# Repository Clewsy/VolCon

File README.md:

# volcon

A USB volume controller that uses a VCR head drum for the knob.

More photos and information can be found [here][link_clews_volcon].

Proudly mentioned at [hackaday.com][link_web_hackaday_volcon], and also on [episode 106][link_web_hackaday_podcast_106] of the [hackaday podcast][link_web_hackaday_podcast].

## Revision 1

This project began as an experiment when I wanted to learn how an optical [quadrature encoder][link_web_quadrature_encoder] worked (FYI, 2-bit [Gray code][link_web_gray_code]).

It transformed into a learning experience around USB - specifically the [HID protocol][link_web_hid].  Ultimately I ended up with a simple gadget that now sits on my desk and allows me to control the PC volume.

A salvaged optical encoder was used to detect rotation along with a reclaimed [head drum][link_web_head_drum] from a [VCR][link_web_vcr] which was repurposed as a control knob. I very much like the smooth bearings combined with the heavy mass that let the drum spin forever.

Key concepts for the project were:

* The optical encoder parts (sensors and disk) were salvaged from an old track-ball.
* The "knob" was made from the head drum of a VHS VCR (remember those?). This is the part that spins and is used to adjust volume on my PC.
* This assembly is mounted to a custom PCB with some nylon stand-offs. The PCB became the base of the whole unit.
* The optical disk was fixed to the shaft and optical sensors mounted to one of the nylon standoffs.
* I cut some wooden rings to enclose the electronics and the base of the VCR drum.
* The original custom PCB was designed in eagle and etched at home from some single-sided copper-clad board. The circuit was designed around an AVR AT90usb162.
* The code is written in C and implements the LUFA library developed by Dean Camera.
* The whole unit plugs into a PC via USB and is automatically identified as a HID - no drivers required (tested in Debian, Ubuntu and Windows).
* It's a very simple device - rotate clockwise to increase volume, counter-clockwise to decrease.

I used the [LUFA][link_web_lufa] (lightweight USB Framework for AVRs) library to implement the USB HID protocol.

After some time (about six years!) of having this device in-use on my desk, I got sick of the simple (ugly) stained pine wood enclosure. With some scrap spotted gum and a router (with a Roman ogee and a roundover bit) I made a slightly nicer enclosure for volcon.

## Revision 2

After even more time, I gave the project an overhaul. Revision 2 uses the same head drum, optical encoder sensors and wooden enclosure. The upgrades from revision 1 include:
* Schematic and PCB layout completely redone but using [KiCad][link_web_kicad] instead of Eagle.
* Microcontroller changed from an AT90usb162 AVR to an ATmega32U4 (simply because I have a few of these).
* Remove the serial Tx/Rx connector (only used this for debugging revision 1).
* Remove the reset tact-switch (also was only used when debugging).
* Use smd components instead of through-hole.
* Connect with a USB type-C connector instead of a USB type-B.
* Have the PCB fabricated (JLCPCB) instead of the home-made copper-etch method.
* A couple of LEDs on the bottom of the PCB purely to visualise the gray code (revision 1 had LEDs, but they only barely shone through etched sections of the PCB).
* Generally improved and cleaner code (still using the LUFA library).

## Revision 2.1

I've been experimenting with 3D prints so I designed and printed a "cap" for the volume controller.  Designed in [freecad][link_web_freecad], printed on a [Prusa CORE One+][link_web_prusa].  CAD files are [here][link_repo_volcon_cap].

![volcon with a 3D-printed cap.][link_image_volcon_cap]
![The completed volcon.][link_image_volcon]

[link_image_volcon]:volcon.jpg
[link_image_volcon_cap]:hardware/cap/volcon_cap.jpg

[link_clews_volcon]:https://clews.pro/projects/volcon.php

[link_repo_volcon_cap]:/hardware/cap/

[link_web_freecad]:https://www.freecad.org/
[link_web_gray_code]:https://en.wikipedia.org/wiki/Gray_code
[link_web_hackaday_podcast]:https://hackaday.com/category/podcasts/
[link_web_hackaday_podcast_106]:https://hackaday.com/2021/02/19/hackaday-podcast-106-connector-kerfuffle-tuning-fork-time-spinach-contact-prints-and-teslas-permanent-memory/
[link_web_hackaday_volcon]:https://hackaday.com/2021/02/15/a-volume-control-from-a-vcr-drum/
[link_web_head_drum]:https://en.wikipedia.org/wiki/File:Kopftrommel_2.jpg
[link_web_hid]:https://en.wikipedia.org/wiki/USB_human_interface_device_class
[link_web_kicad]:https://www.kicad.org/
[link_web_lufa]:http://fourwalledcubicle.com/LUFA.php
[link_web_prusa]:https://www.prusa3d.com/
[link_web_quadrature_encoder]:https://en.wikipedia.org/wiki/Quadrature_encoder
[link_web_vcr]:https://en.wikipedia.org/wiki/Videocassette_recorder

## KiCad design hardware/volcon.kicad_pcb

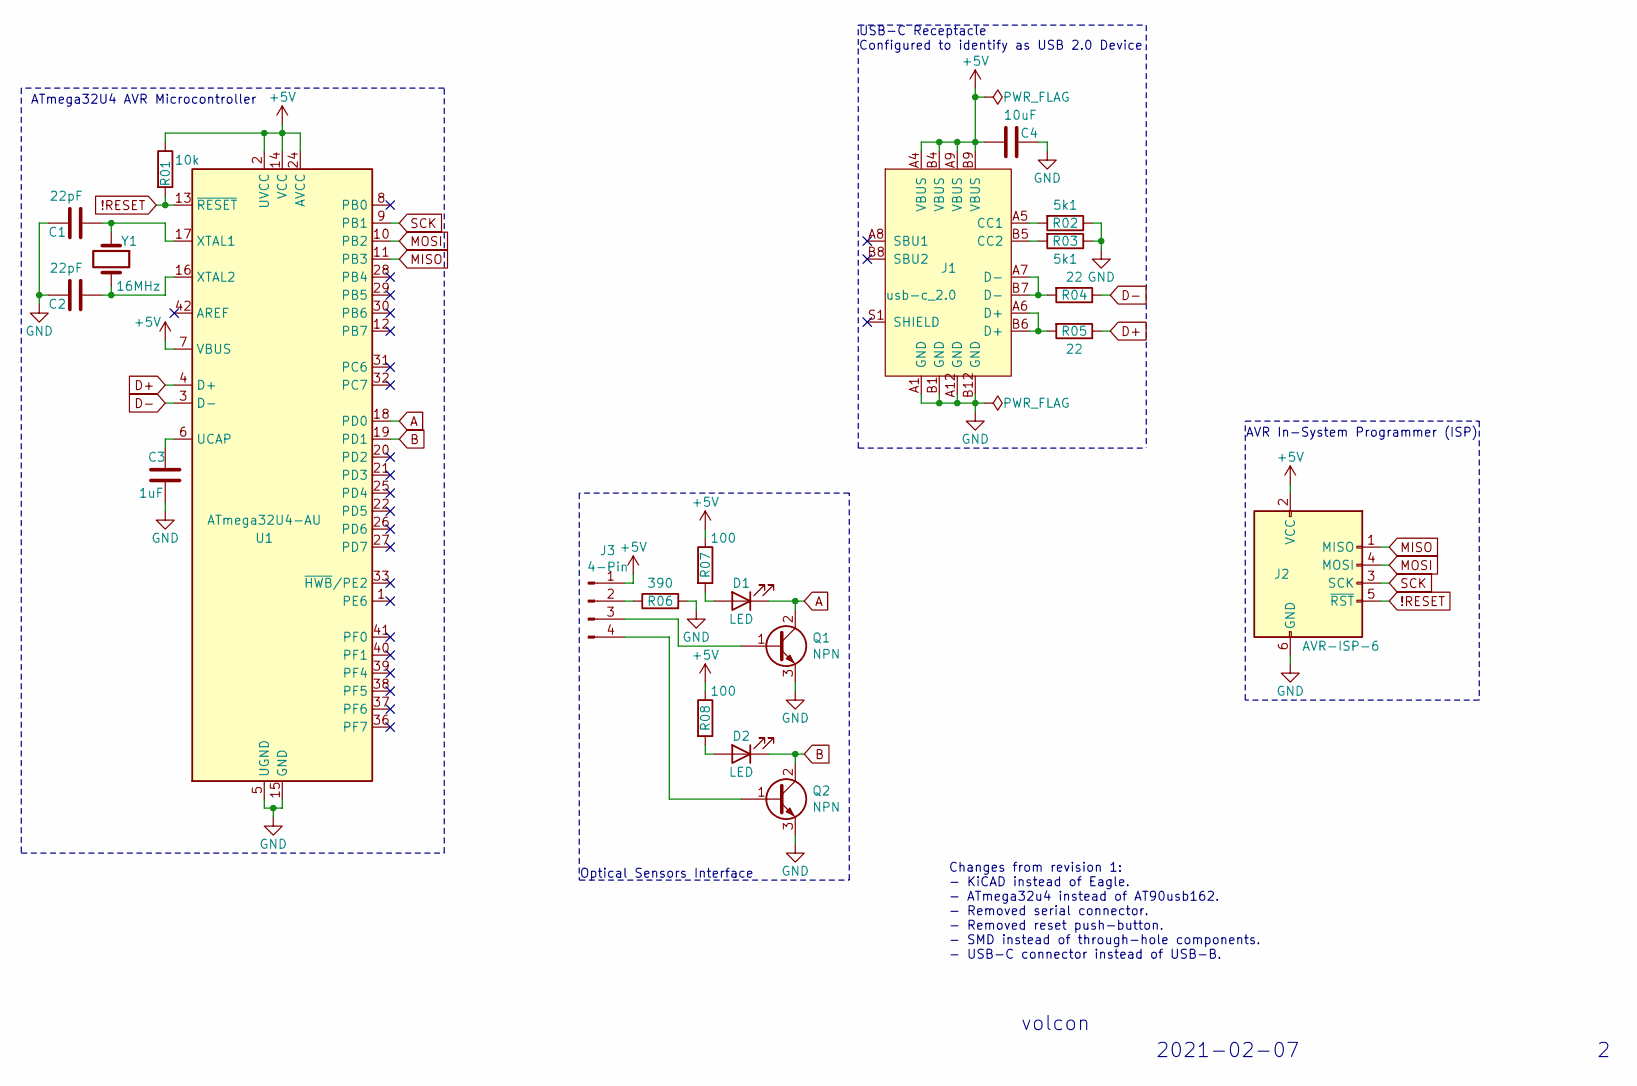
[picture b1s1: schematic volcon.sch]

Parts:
C1, C2: 22pF; C_1206_3216Metric_Pad1.42x1.75mm_HandSolder
C3: 1uF; C_1206_3216Metric_Pad1.42x1.75mm_HandSolder
C4: 10uF; C_1206_3216Metric_Pad1.42x1.75mm_HandSolder
D1, D2: LED; LED_Cree-XQ_HandSoldering
J1: usb-c_2.0; USB_C_Receptacle_GCT_USB4085
J2: AVR-ISP-6; IDC-Header_2x03_P2.54mm_Vertical
J3: 4-Pin; PinHeader_1x04_P2.54mm_Vertical
Q1, Q2: NPN; SOT-223-3_TabPin2
R01: 10k; R_1206_3216Metric_Pad1.42x1.75mm_HandSolder
R02, R03: 5k1; R_1206_3216Metric_Pad1.42x1.75mm_HandSolder
R04, R05: 22; R_1206_3216Metric_Pad1.42x1.75mm_HandSolder
R06: 390; R_1206_3216Metric_Pad1.42x1.75mm_HandSolder
R07, R08: 100; R_1206_3216Metric_Pad1.42x1.75mm_HandSolder
U1: ATmega32U4-AU; TQFP-44_10x10mm_P0.8mm
Y1: 16MHz; Crystal_SMD_HC49-SD

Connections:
!RESET: J2.5 (~RST), R01.2, U1.13 (~RESET)
+5V: C4.2, J1.A4 (VBUS), J1.A9 (VBUS), J1.B4 (VBUS), J1.B9 (VBUS), J2.2 (VCC), J3.1, R01.1, R07.1, R08.1, U1.2 (UVCC), U1.7 (VBUS), U1.14 (VCC), U1.24 (AVCC), U1.34 (VCC), U1.44 (AVCC)
A: D1.1 (K), Q1.2 (C), U1.18 (PD0)
B: D2.1 (K), Q2.2 (C), U1.19 (PD1)
D+: R05.1, U1.4 (D+)
D-: R04.1, U1.3 (D-)
GND: C1.2, C2.2, C3.2, C4.1, J1.A1 (GND), J1.A12 (GND), J1.B1 (GND), J1.B12 (GND), J2.6 (GND), Q1.3 (E), Q2.3 (E), R02.1, R03.1, R06.2, U1.5 (UGND), U1.15 (GND), U1.23 (GND), U1.35 (GND), U1.43 (GND)
MISO: J2.1 (MISO), U1.11 (PB3)
MOSI: J2.4 (MOSI), U1.10 (PB2)
unnamed: C1.1, U1.17 (XTAL1), Y1.1
unnamed: C2.1, U1.16 (XTAL2), Y1.2
unnamed: C3.1, U1.6 (UCAP)
unnamed: D1.2 (A), R07.2
unnamed: D2.2 (A), R08.2
unnamed: J1.A5 (CC1), R02.2
unnamed: J1.A6 (D+), J1.B6 (D+), R05.2
unnamed: J1.A7 (D-), J1.B7 (D-), R04.2
unnamed: J1.B5 (CC2), R03.2
unnamed: J3.2, R06.1
unnamed: J3.3, Q1.1 (B)
unnamed: J3.4, Q2.1 (B)
SCK: J2.3 (SCK), U1.9 (PB1)

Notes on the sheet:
volcon
2021-02-07
ATmega32U4 AVR Microcontroller
Optical Sensors Interface
AVR In-System Programmer (ISP)
USB-C Receptacle Configured to identify as USB 2.0 Device
Changes from revision 1: - KiCAD instead of Eagle. - ATmega32u4 instead of AT90usb162. - Removed serial connector. - Removed reset push-button. - SMD instead of through-hole components. - USB-C connector instead of USB-B.

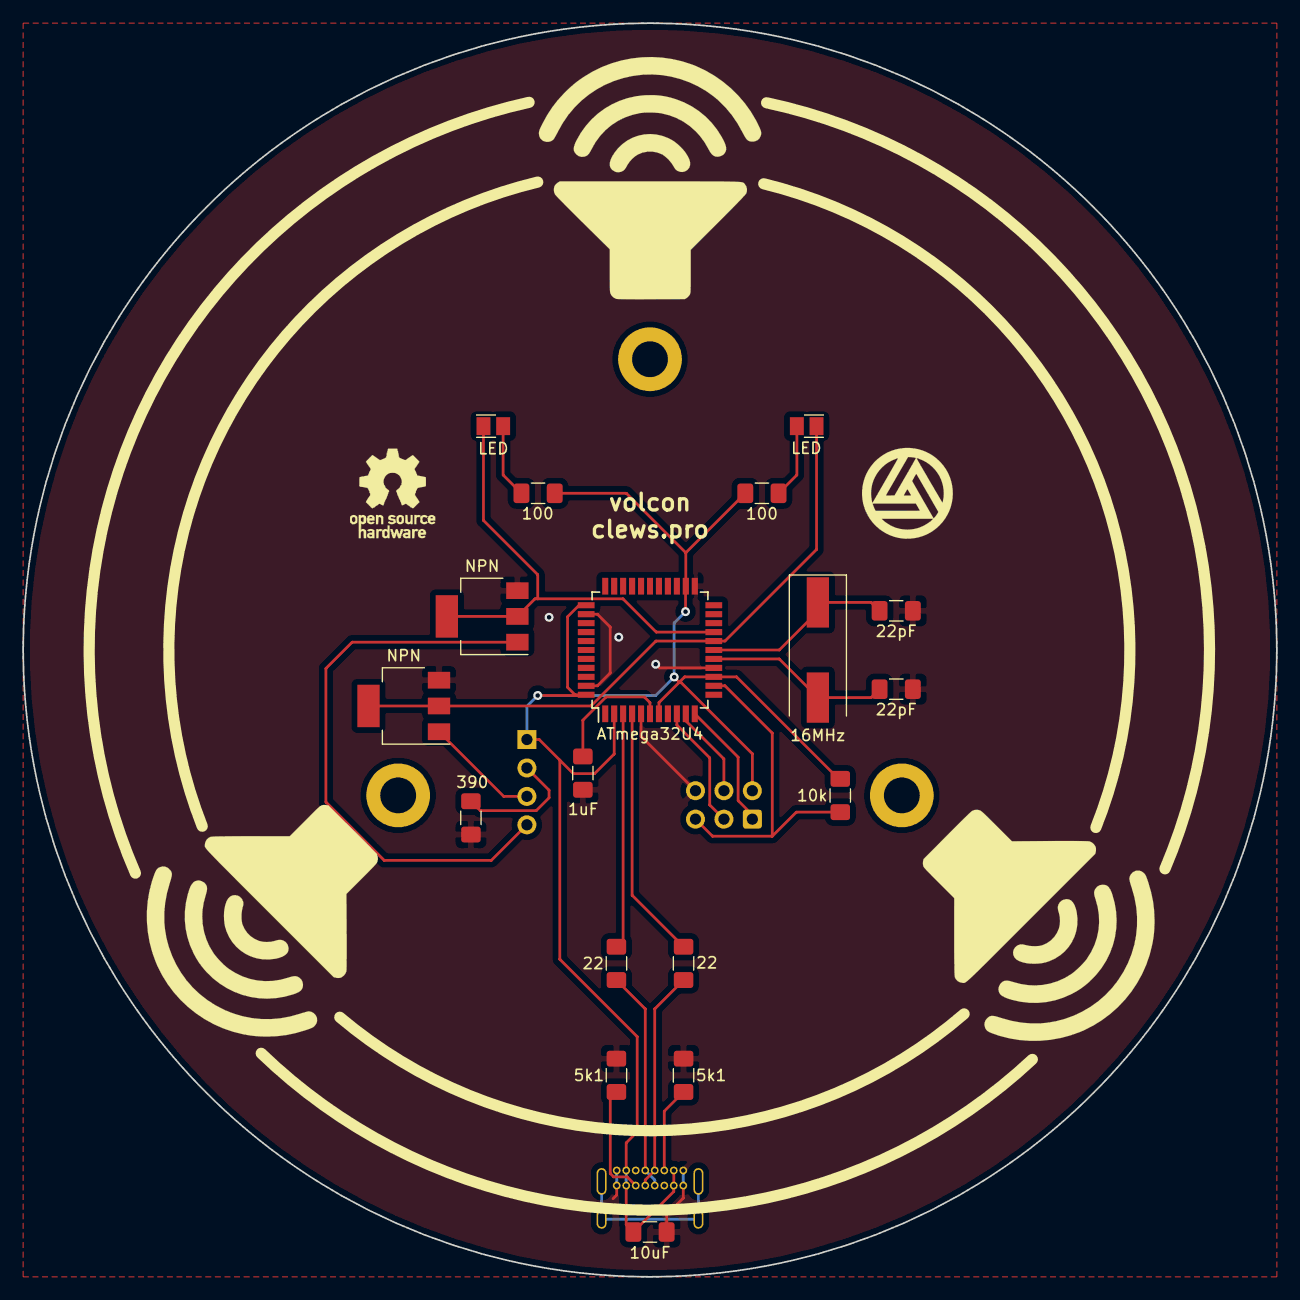
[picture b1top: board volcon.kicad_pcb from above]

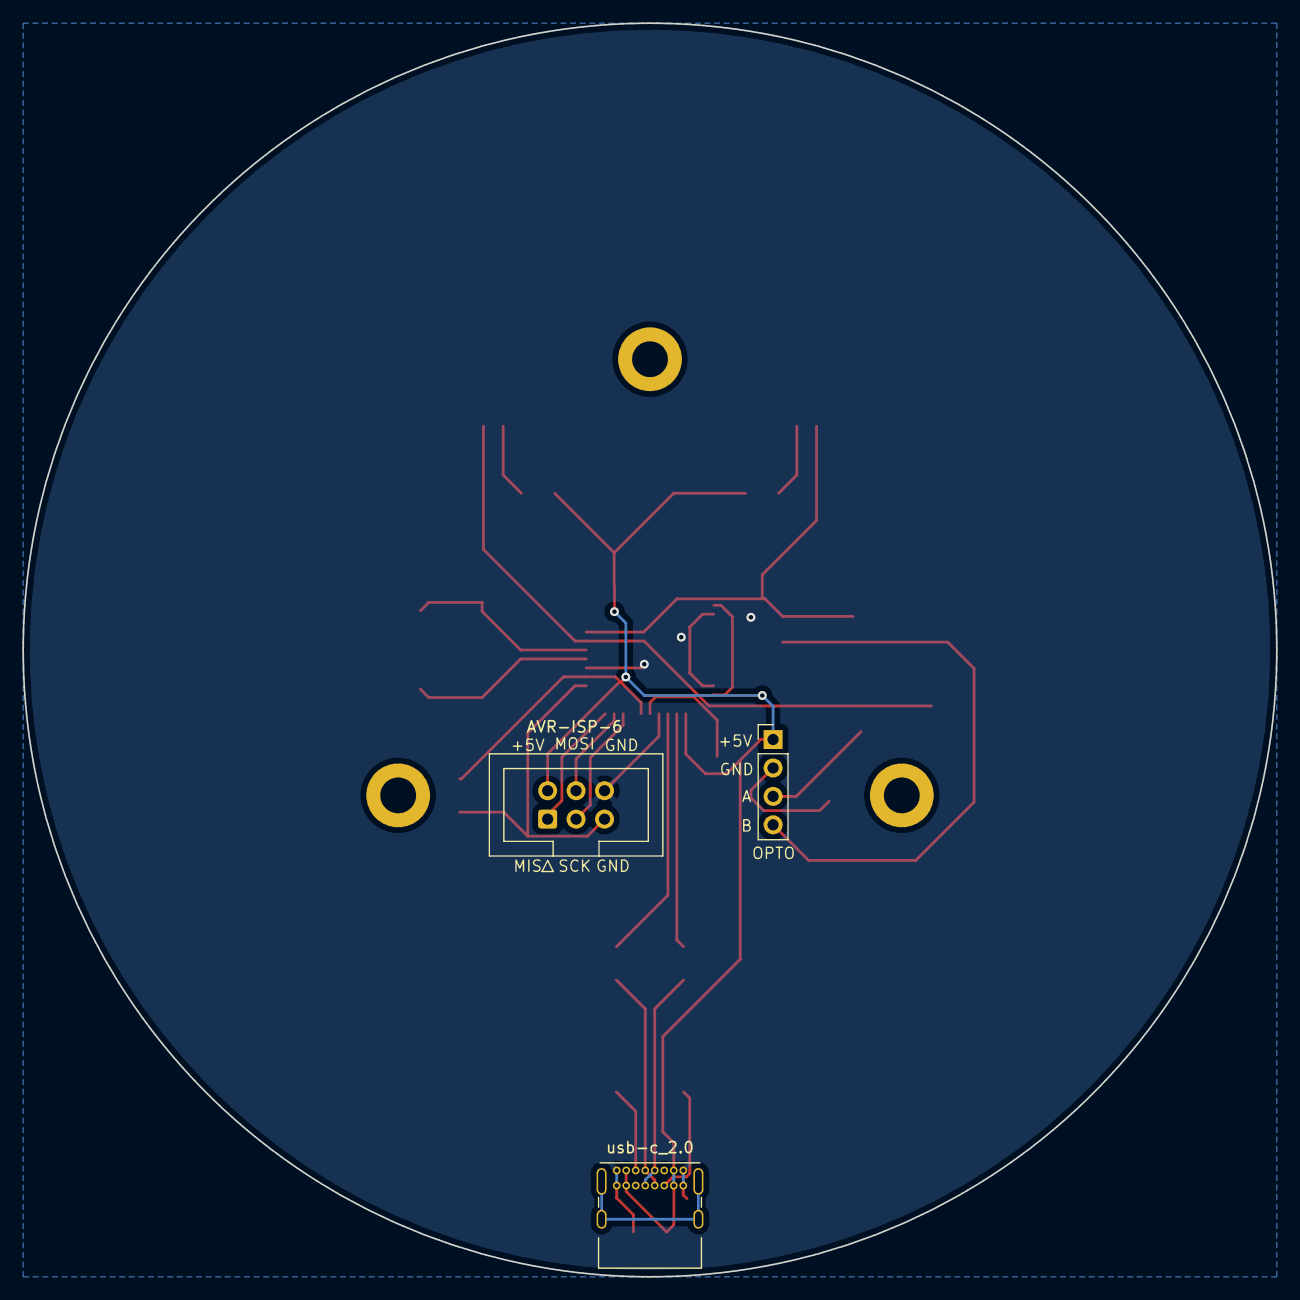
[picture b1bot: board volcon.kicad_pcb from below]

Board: 2 copper layers, 112.0 x 112.0 mm, 21 parts (3 on the bottom side), 22 nets.

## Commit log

2021-01-26 Beginning a second revision.
2021-01-26 Compressed earlier revision.
2021-01-26 Ignore exported gerber files.
2021-01-26 Transistor datasheet.
2021-01-27 Datasheets.
2021-01-28 Crystal datasheet.
2021-02-06 Hobbled code together from other projects. Basic functionality working, time to clean it up.
2021-02-06 Clean-up and efficiencies.
2021-02-06 Code is in pretty good shape.
2021-02-07 Minor adjustments, clean-up and comments. Generated schematic pdf for repo.
2021-02-11 Readme and photo.
2021-02-11 Embed photo in readme.
2021-02-12 Fixed some comment typos and tidied some code for readability.
2021-02-13 Add vscode c_cpp_propoerties to repo - better intellisense results.
2021-02-21 Revised readme. Added links to hackaday article and hackaday podcast.
2026-06-20 3d-printed cap
